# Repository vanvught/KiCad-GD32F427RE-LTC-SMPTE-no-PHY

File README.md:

# KiCad GD32F427RE LTC-SMPTE no PHY

Firmware [https://github.com/vanvught/GD32F427RE-LTC-SMPTE](https://github.com/vanvught/GD32F427RE-LTC-SMPTE)

More information [https://www.gd32-dmx.org](https://www.gd32-dmx.org)

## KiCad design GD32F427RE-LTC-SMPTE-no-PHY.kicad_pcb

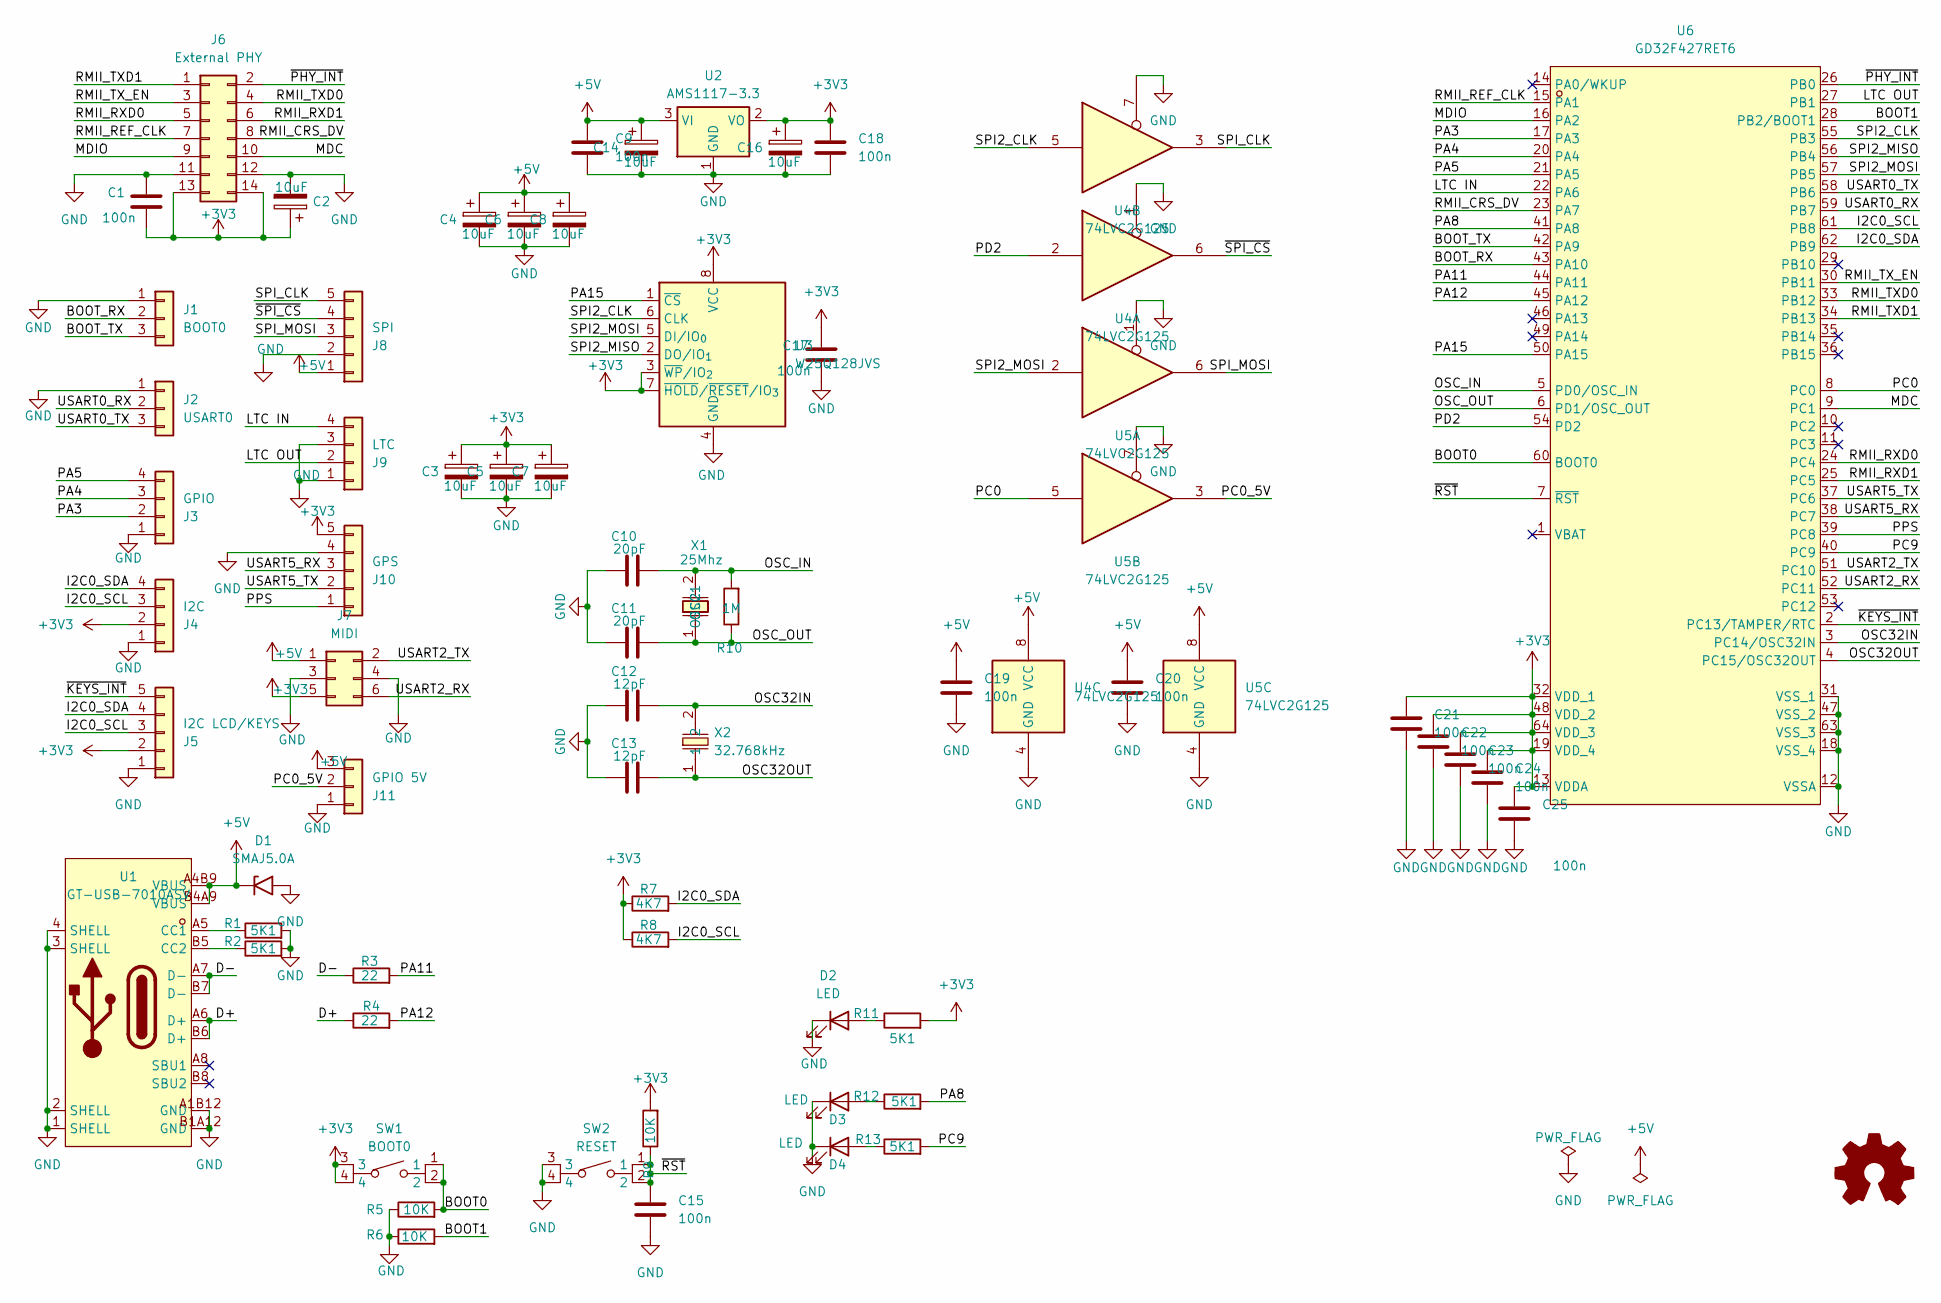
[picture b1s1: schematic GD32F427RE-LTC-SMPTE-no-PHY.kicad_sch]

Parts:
C1, C9, C15, C17, C18, C19, C20, C21, C22, C23, C24, C25: 100n; C_0603_1608Metric; LCSC Part C14663
C2, C3, C4, C5, C6, C7, C8, C14, C16: 10uF; CP_EIA-3216-18_Kemet-A; LCSC Part C7171
C10, C11: 20pF; C_0603_1608Metric; LCSC Part C1648
C12, C13: 12pF; C_0603_1608Metric; LCSC Part C38523
D1: SMAJ5.0A; D_SMA; LCSC Part C113952
D2, D3, D4: LED; LED_0805_2012Metric; LCSC Part C2297
J1: BOOT0; PinHeader_1x03_P2.54mm_Vertical
J2: USART0; PinHeader_1x03_P2.54mm_Vertical
J3: GPIO; PinHeader_1x04_P2.54mm_Vertical
J4: I2C; PinHeader_1x04_P2.54mm_Vertical
J5: I2C LCD/KEYS; PinHeader_1x05_P2.54mm_Vertical
J6: External PHY; PinSocket_2x07_P2.54mm_Horizontal
J7: MIDI; PinHeader_2x03_P2.54mm_Vertical
J8: SPI; PinHeader_1x05_P2.54mm_Vertical
J9: LTC; PinHeader_1x04_P2.54mm_Vertical
J10: GPS; PinHeader_1x05_P2.54mm_Vertical
J11: GPIO 5V; PinHeader_1x03_P2.54mm_Vertical
R1, R2, R11, R12, R13: 5K1; R_0603_1608Metric; LCSC Part C23186
R3, R4: 22; R_0603_1608Metric; LCSC Part C23345
R5, R6, R9: 10K; R_0603_1608Metric; LCSC Part C25804
R7, R8: 4K7; R_0603_1608Metric; LCSC Part C23162
R10: 1M; R_0603_1608Metric; LCSC Part C22935
SW1: BOOT0; KEY-SMD_4P-L6.0-W6.0-P4.50-LS9.0; MPN PTS645SM43SMTR92LFS; LCSC Part C221880
SW2: RESET; KEY-SMD_4P-L6.0-W6.0-P4.50-LS9.0; MPN PTS645SM43SMTR92LFS; LCSC Part C221880
SYM1: Logo_Open_Hardware_Small; OSHW-Logo_5.7x6mm_SilkScreen
U1: GT-USB-7010ASV; USB-C-SMD_G-SWITCH_GT-USB-7010ASV; MPN GT-USB-7010ASV; LCSC Part C2988369
U2: AMS1117-3.3; SOT-223-3_TabPin2
U3: W25Q128JVS; SOIC-8_5.3x5.3mm_P1.27mm; LCSC Part C97521
U4, U5: 74LVC2G125; SM8_L3.2-W2.9-P0.65-LS4.3-BR; LCSC Part C206035
U6: GD32F427RET6; LQFP-64_L10.0-W10.0-P0.50-LS12.0-BL; MPN GD32F407RET6; LCSC Part C2688748
X1: 25Mhz; HC-49S_L11.4-W4.8; MPN X49SM25MSD2SC; LCSC Part C14872
X2: 32.768kHz; FC-135R_L3.2-W1.5; MPN Q13FC13500004; LCSC Part C32346

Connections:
+3V3: C1.2, C2.1, C3.1, C5.1, C7.1, C16.1, C17.1, C18.1, C21.1, C22.1, C23.1, C24.1, C25.1, J4.2, J5.2, J6.13, J6.14, J7.5, J10.5, R7.1, R8.1, R9.2, R11.2, SW1.3, SW1.4, U2.2 (VO), U3.3 (~WP/IO_{2}), U3.7 (~HOLD/~RESET/IO_{3}), U3.8 (VCC), U6.13 (VDDA), U6.19 (VDD_4), U6.32 (VDD_1), U6.48 (VDD_2), U6.64 (VDD_3)
+5V: C4.1, C6.1, C8.1, C9.1, C14.1, C19.1, C20.1, D1.1 (A1), J7.1, J8.1, J11.3, U1.A4B9 (VBUS), U1.B4A9 (VBUS), U2.3 (VI), U4.8 (VCC), U5.8 (VCC)
/BOOT0: R5.2, SW1.1, SW1.2, U6.60 (BOOT0)
/BOOT1: R6.2, U6.28 (PB2/BOOT1)
/BOOT_RX: J1.2, U6.43 (PA10)
/BOOT_TX: J1.3, U6.42 (PA9)
/D+: R4.1, U1.A6 (D+), U1.B6 (D+)
/D-: R3.1, U1.A7 (D-), U1.B7 (D-)
/I2C0_SCL: J4.3, J5.3, R8.2, U6.61 (PB8)
/I2C0_SDA: J4.4, J5.4, R7.2, U6.62 (PB9)
/LTC IN: J9.4, U6.22 (PA6)
/LTC OUT: J9.2, U6.27 (PB1)
/MDC: J6.10, U6.9 (PC1)
/MDIO: J6.9, U6.16 (PA2)
/OSC32IN: C12.2, U6.3 (PC14/OSC32IN), X2.2
/OSC32OUT: C13.2, U6.4 (PC15/OSC32OUT), X2.1
/OSC_IN: C10.2, R10.2, U6.5 (PD0/OSC_IN), X1.2 (OSC2)
/OSC_OUT: C11.2, R10.1, U6.6 (PD1/OSC_OUT), X1.1 (OSC1)
/PA3: J3.2, U6.17 (PA3)
/PA4: J3.3, U6.20 (PA4)
/PA5: J3.4, U6.21 (PA5)
/PA8: R12.2, U6.41 (PA8)
/PA11: R3.2, U6.44 (PA11)
/PA12: R4.2, U6.45 (PA12)
/PA15: U3.1 (~CS), U6.50 (PA15)
/PC0: U5.5, U6.8 (PC0)
/PC0_5V: J11.2, U5.3
/PC9: R13.2, U6.40 (PC9)
/PD2: U4.2, U6.54 (PD2)
/PPS: J10.1, U6.39 (PC8)
/RMII_CRS_DV: J6.8, U6.23 (PA7)
/RMII_REF_CLK: J6.7, U6.15 (PA1)
/RMII_RXD0: J6.5, U6.24 (PC4)
/RMII_RXD1: J6.6, U6.25 (PC5)
/RMII_TXD0: J6.4, U6.33 (PB12)
/RMII_TXD1: J6.1, U6.34 (PB13)
/RMII_TX_EN: J6.3, U6.30 (PB11)
/SPI2_CLK: U3.6 (CLK), U4.5, U6.55 (PB3)
/SPI2_MISO: U3.2 (DO/IO_{1}), U6.56 (PB4)
/SPI2_MOSI: U3.5 (DI/IO_{0}), U5.2, U6.57 (PB5)
/SPI_CLK: J8.5, U4.3
/SPI_MOSI: J8.3, U5.6
/USART0_RX: J2.2, U6.59 (PB7)
/USART0_TX: J2.3, U6.58 (PB6)
/USART2_RX: J7.6, U6.52 (PC11)
/USART2_TX: J7.2, U6.51 (PC10)
/USART5_RX: J10.3, U6.38 (PC7)
/USART5_TX: J10.2, U6.37 (PC6)
/~KEYS_INT: J5.5, U6.2 (PC13/TAMPER/RTC)
/~PHY_INT: J6.2, U6.26 (PB0)
/~RST: C15.1, R9.1, SW2.1, SW2.2, U6.7 (~RST)
/~SPI_CS: J8.4, U4.6
GND: C1.1, C2.2, C3.2, C4.2, C5.2, C6.2, C7.2, C8.2, C9.2, C10.1, C11.1, C12.1, C13.1, C14.2, C15.2, C16.2, C17.2, C18.2, C19.2, C20.2, C21.2, C22.2, C23.2, C24.2, C25.2, D1.2 (A2), D2.1 (K), D3.1 (K), D4.1 (K), J1.1, J2.1, J3.1, J4.1, J5.1, J6.11, J6.12, J7.3, J7.4, J8.2, J9.1, J9.3, J10.4, J11.1, R1.2, R2.2, R5.1, R6.1, SW2.3, SW2.4, U1.1 (SHELL), U1.2 (SHELL), U1.3 (SHELL), U1.4 (SHELL), U1.A1B12 (GND), U1.B1A12 (GND), U2.1 (GND), U3.4 (GND), U4.1, U4.4 (GND), U4.7, U5.1, U5.4 (GND), U5.7, U6.12 (VSSA), U6.18 (VSS_4), U6.31 (VSS_1), U6.47 (VSS_2), U6.63 (VSS_3)
unnamed: D2.2 (A), R11.1
unnamed: D3.2 (A), R12.1
unnamed: D4.2 (A), R13.1
unnamed: R1.1, U1.A5 (CC1)
unnamed: R2.1, U1.B5 (CC2)

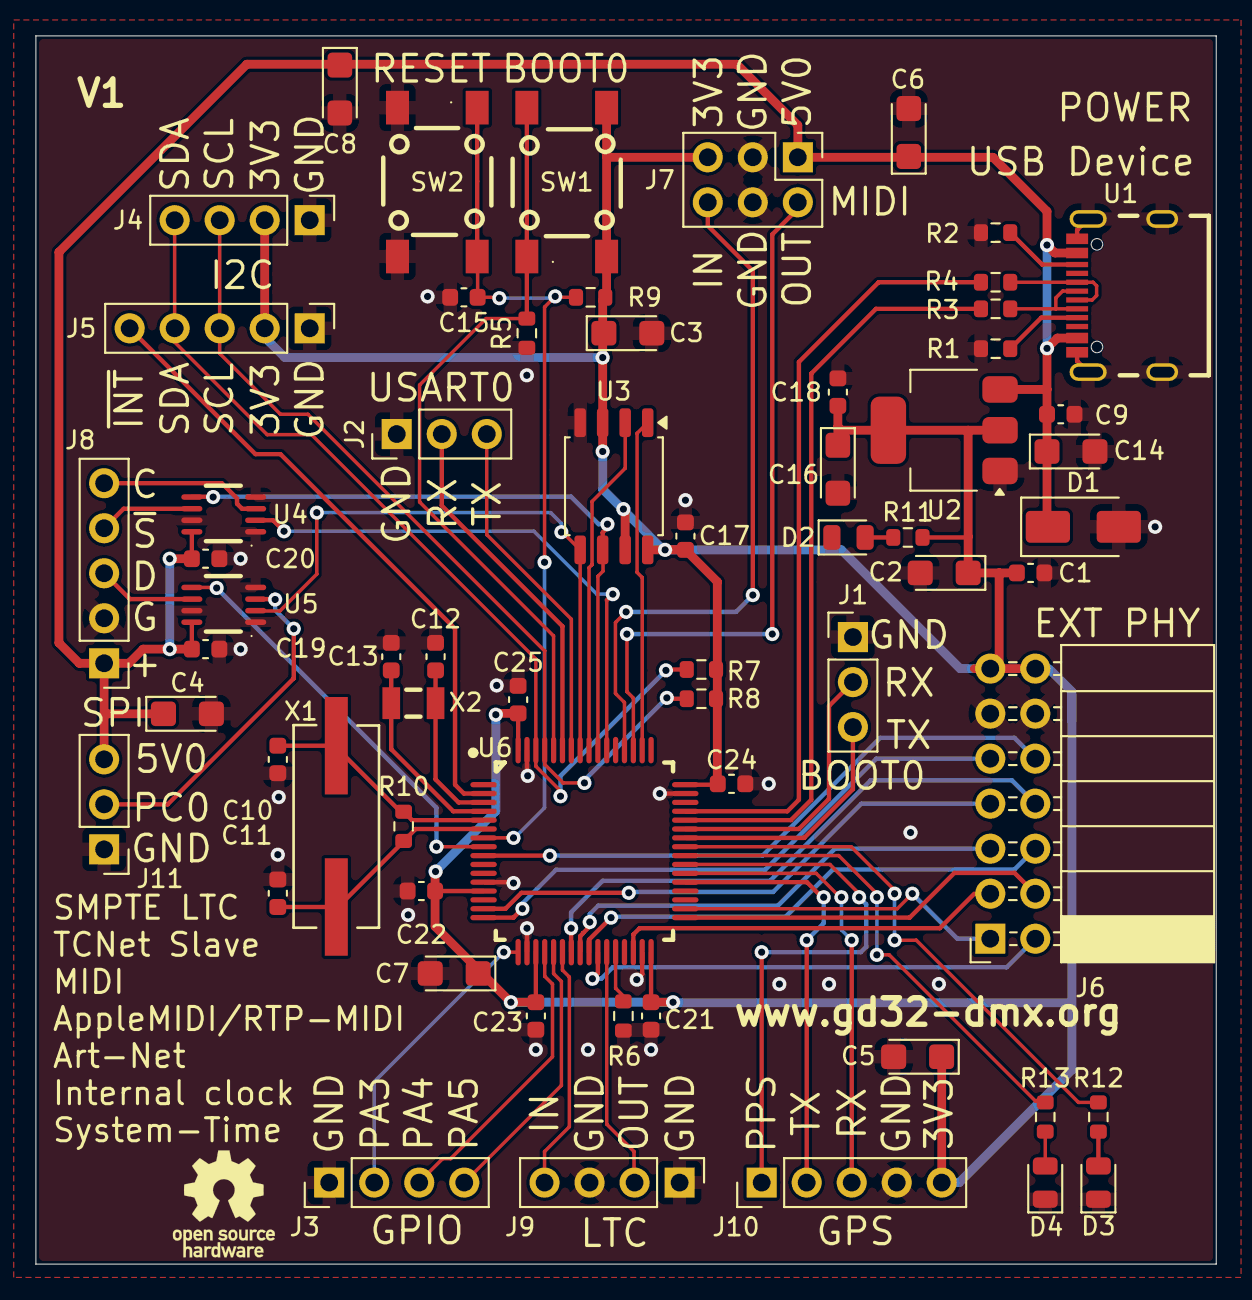
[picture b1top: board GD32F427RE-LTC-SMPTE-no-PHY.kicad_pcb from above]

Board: 2 copper layers, 66.6 x 69.3 mm, 64 parts (0 on the bottom side), 58 nets.
